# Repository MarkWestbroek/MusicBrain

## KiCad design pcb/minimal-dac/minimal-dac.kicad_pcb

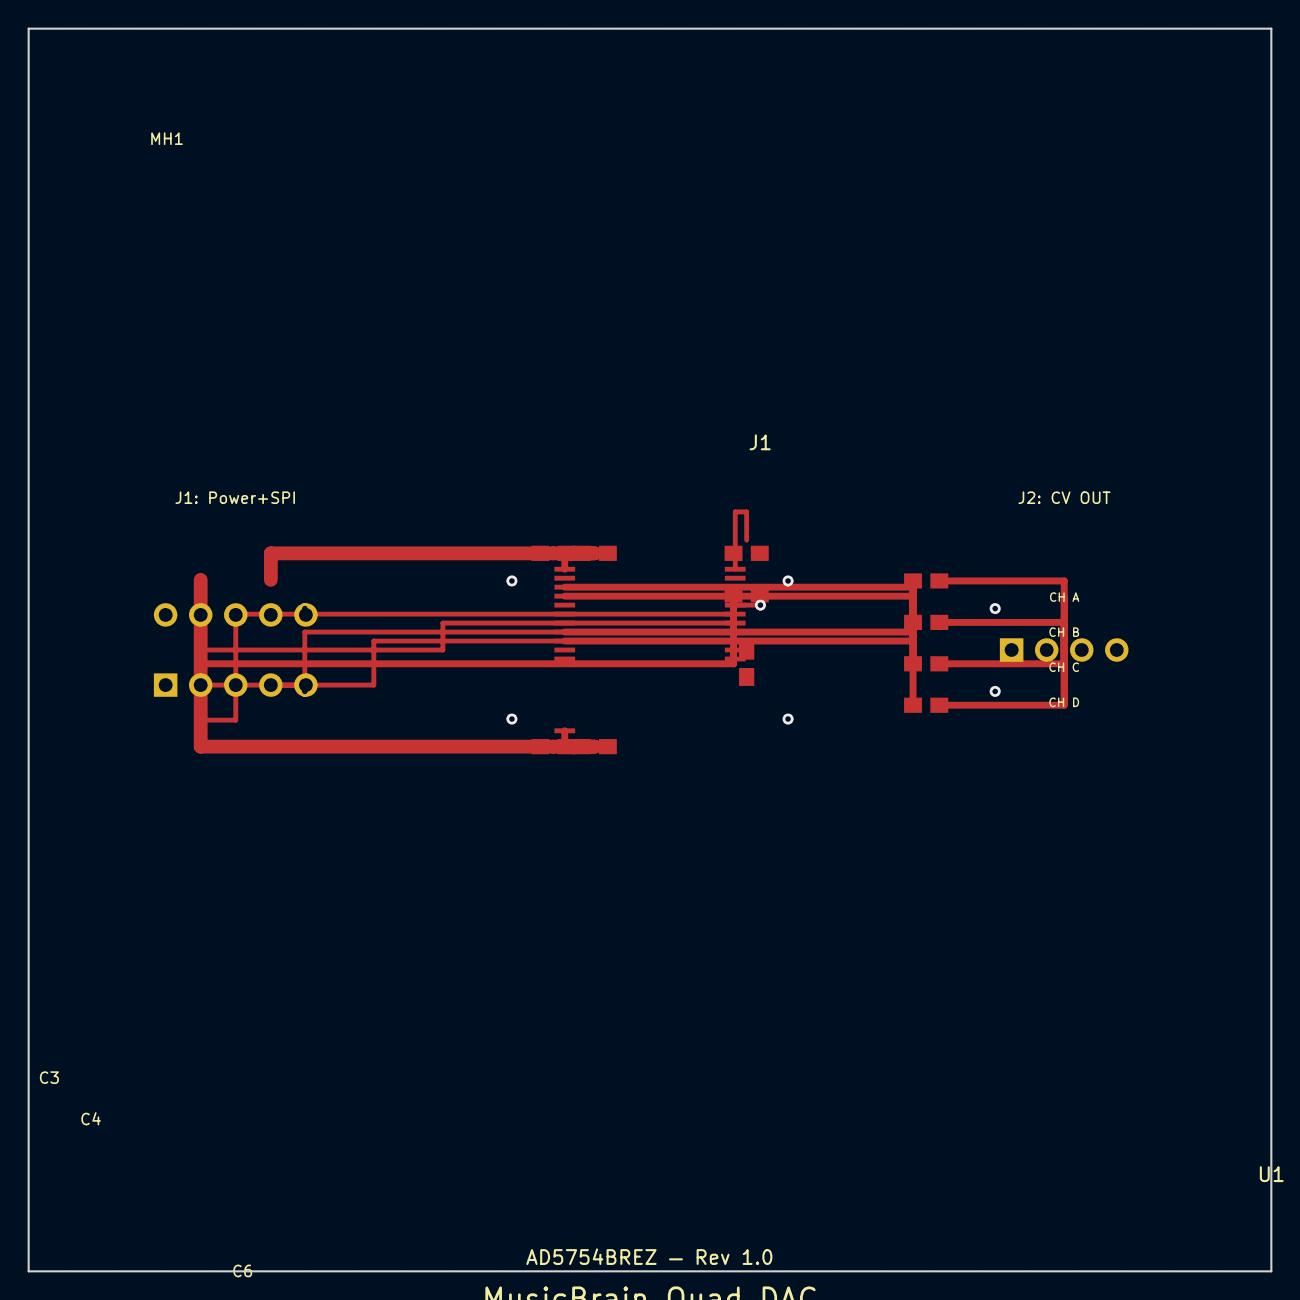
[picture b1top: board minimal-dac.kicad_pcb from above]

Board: 4 copper layers, 90.0 x 90.0 mm, 18 parts (0 on the bottom side), 14 nets.

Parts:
C1, C3: 10µF; C_0805_2012Metric
C2, C4, C5, C6: 0.1µF; C_0805_2012Metric
J1: Power+SPI; PinHeader_2x05_P2.54mm_Vertical
J2: CV_OUT; PinHeader_1x04_P2.54mm_Vertical
MH1, MH2, MH3, MH4: MountingHole_3.2mm_M3
R1: 10kΩ; R_0805_2012Metric
R2, R3, R4, R5: 47Ω; R_0805_2012Metric
U1: AD5754BREZ; TSSOP-24_4.4x7.8mm_P0.65mm

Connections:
+3V3: C5.1, J1.3, R1.1, U1.14
+12V: C1.1, C2.1, J1.1, U1.24
-12V: C3.2, C4.2, J1.2, U1.1
CLR: R1.2, U1.11
CS: J1.9, U1.7
GND: C1.2, C2.2, C3.1, C4.1, C5.2, C6.1, J1.4, J1.6, J1.10, U1.10, U1.15, U1.18, U1.19, U1.20, U1.21
MISO: J1.8, U1.16
MOSI: J1.5, U1.9
REFIN: C6.2, U1.17
SCK: J1.7, U1.8
VOUT_A: J2.1, R2.1, R2.2, U1.3
VOUT_B: J2.2, R3.1, R3.2, U1.4
VOUT_C: J2.3, R4.1, R4.2, U1.23
VOUT_D: J2.4, R5.1, R5.2, U1.22
